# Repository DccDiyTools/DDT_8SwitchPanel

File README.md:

# DDT_8SwitchPanel
Ui Panel for 8 Rocket Switches

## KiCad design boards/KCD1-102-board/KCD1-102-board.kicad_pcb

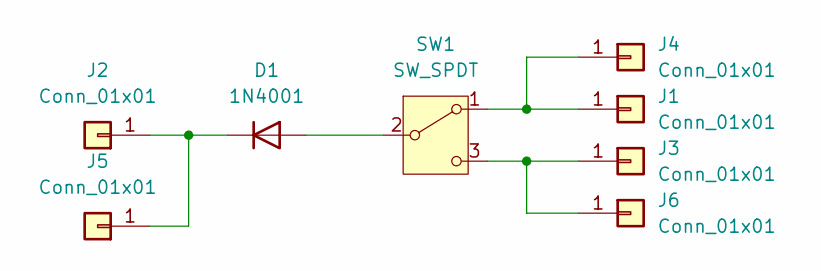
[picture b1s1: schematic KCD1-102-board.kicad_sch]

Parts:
D1: 1N4001; D_1206_3216Metric_Pad1.42x1.75mm_HandSolder
J1, J2, J3: Conn_01x01; SolderWirePad_1x01_SMD_1x2mm
J4, J5, J6: Conn_01x01; SolderWirePad_1x01_SMD_5x10mm
SW1: SW_SPDT; KCD1-102

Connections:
unnamed: D1.2 (A), SW1.2 (B)
unnamed: D1.1 (K), J2.1, J5.1
unnamed: J1.1, J4.1, SW1.1 (A)
unnamed: J3.1, J6.1, SW1.3 (C)

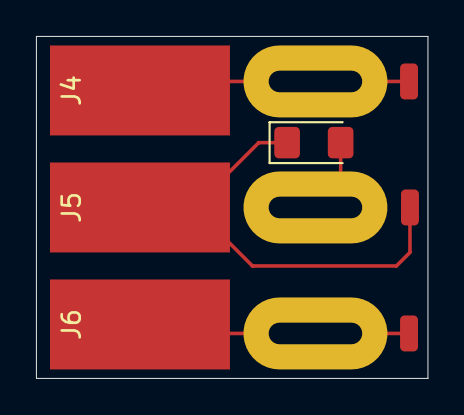
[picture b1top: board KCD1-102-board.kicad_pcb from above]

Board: 2 copper layers, 21.8 x 19.0 mm, 8 parts (1 on the bottom side), 4 nets.

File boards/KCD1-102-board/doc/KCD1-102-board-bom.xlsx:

|  | Bill of Materials
 |  | Schematic: | KCD1-102-board | Component Groups: | 4
 |  | Variant: | default | Component Count: | 8 (7 SMD/ 1 THT)
 |  | Revision: |  | Fitted Components: | 8 (7 SMD/ 1 THT)
 |  | Date: | 2024-10-21_11-48-44 | Number of PCBs: | 1
 |  | KiCad Version: | 8.0.4+1 | Total Components: | 8
Row | Description | Part | References | Value | Footprint | Quantity Per PCB | Status | Datasheet | Sim.Device | Sim.Pins
1 | 50V 1A General Purpose Rectifier Diode, DO-41 | 1N4001 | D1 | 1N4001 | D_1206_3216Metric_Pad1.42x1.75mm_HandSolder | 1 |  | http://www.vishay.com/docs/88503/1n4001.pdf | D | 1=K 2=A
2 | Generic connector, single row, 01x01, script generated (kicad-library-utils/sch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 | Conn_01x01 | J1 J2 J3 | Conn_01x01 | SolderWirePad_1x01_SMD_1x2mm | 3 |  | ~
3 | Generic connector, single row, 01x01, script generated (kicad-library-utils/sch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 | Conn_01x01 | J4 J5 J6 | Conn_01x01 | SolderWirePad_1x01_SMD_5x10mm | 3 |  | ~
4 | Switch, single pole double throw | SW_SPDT | SW1 | SW_SPDT | KCD1-102 | 1 |  | ~

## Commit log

2024-10-07 First Basic Control
2024-10-17 Basic Work
2024-10-21 Rename for switch board
2024-10-21 Estudio Panel rocket Switch
